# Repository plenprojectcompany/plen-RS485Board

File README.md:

RS485 Board | PLEN Project Company Inc.
===============================================================================

## Copyright (c) 2015,
- [PLEN Project Company Inc.](https://plen.jp)
- Naohiro HAYAISHI
- [Mitsuhiro MIYAGUCHI](https://github.com/mitsuhiromiyaguchi)

## Build Environment
- Windows 8.1
- Eagle 6.60

## License
This material is released under the [Creative Commons BY 4.0](http://creativecommons.org/licenses/by/4.0/).

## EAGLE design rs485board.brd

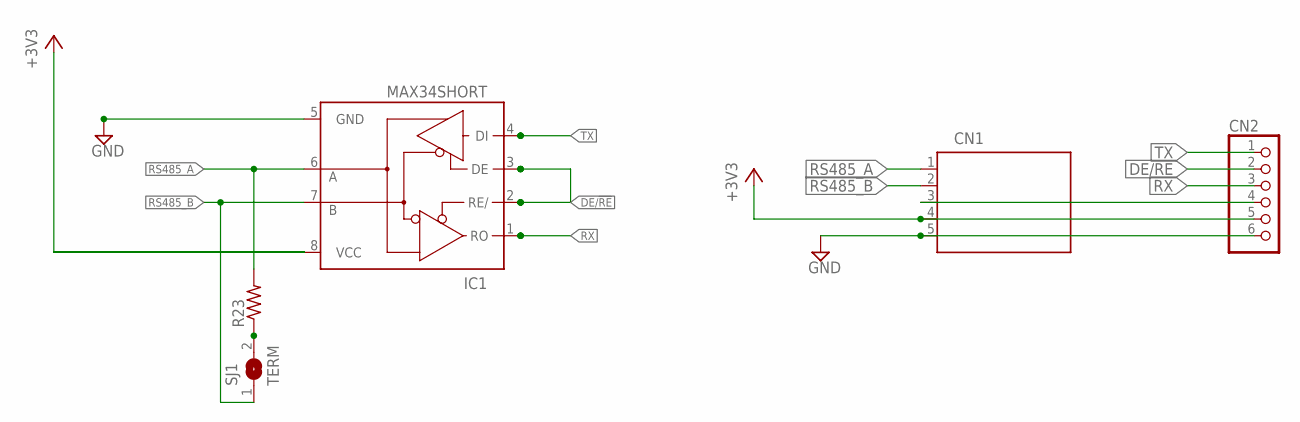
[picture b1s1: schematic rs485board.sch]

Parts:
CN1: 5PINZH; ZH-5
CN2: PINHD-1X06_2.54; 1X06
IC1: MAX34SHORT; SO08SHORT
R23: R-US_R0603; R0603
SJ1: TERM; SJ

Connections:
+3V3RS485: CN1.4, CN2.5, IC1.8 (VCC)
DE/!RE: CN2.2, IC1.2 (RE/), IC1.3 (DE)
GND: CN1.5, CN2.6, IC1.5 (GND)
unnamed: R23.1, SJ1.2
unnamed: CN1.3, CN2.4
RS485_A: CN1.1, IC1.6 (A), R23.2
RS485_B: CN1.2, IC1.7 (B), SJ1.1
RX: CN2.3, IC1.1 (RO)
TX: CN2.1, IC1.4 (DI)

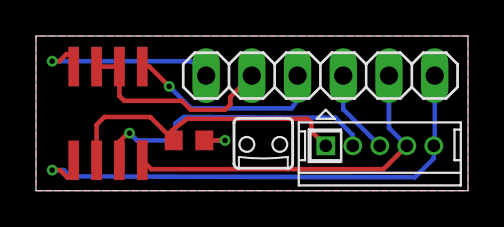
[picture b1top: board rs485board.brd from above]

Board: 2 copper layers, 24.0 x 8.6 mm, 6 parts (1 on the bottom side), 9 nets.

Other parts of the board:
U$3: PLENLOGO

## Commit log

2015-08-30 First commit.
2015-08-31 Fix LICENSE.md.
2015-08-31 Fix README.md.
2016-04-14 Fix documents
2017-01-17 Update documents
2017-01-17 Change layout
2018-04-19 Update copyright & contributors
